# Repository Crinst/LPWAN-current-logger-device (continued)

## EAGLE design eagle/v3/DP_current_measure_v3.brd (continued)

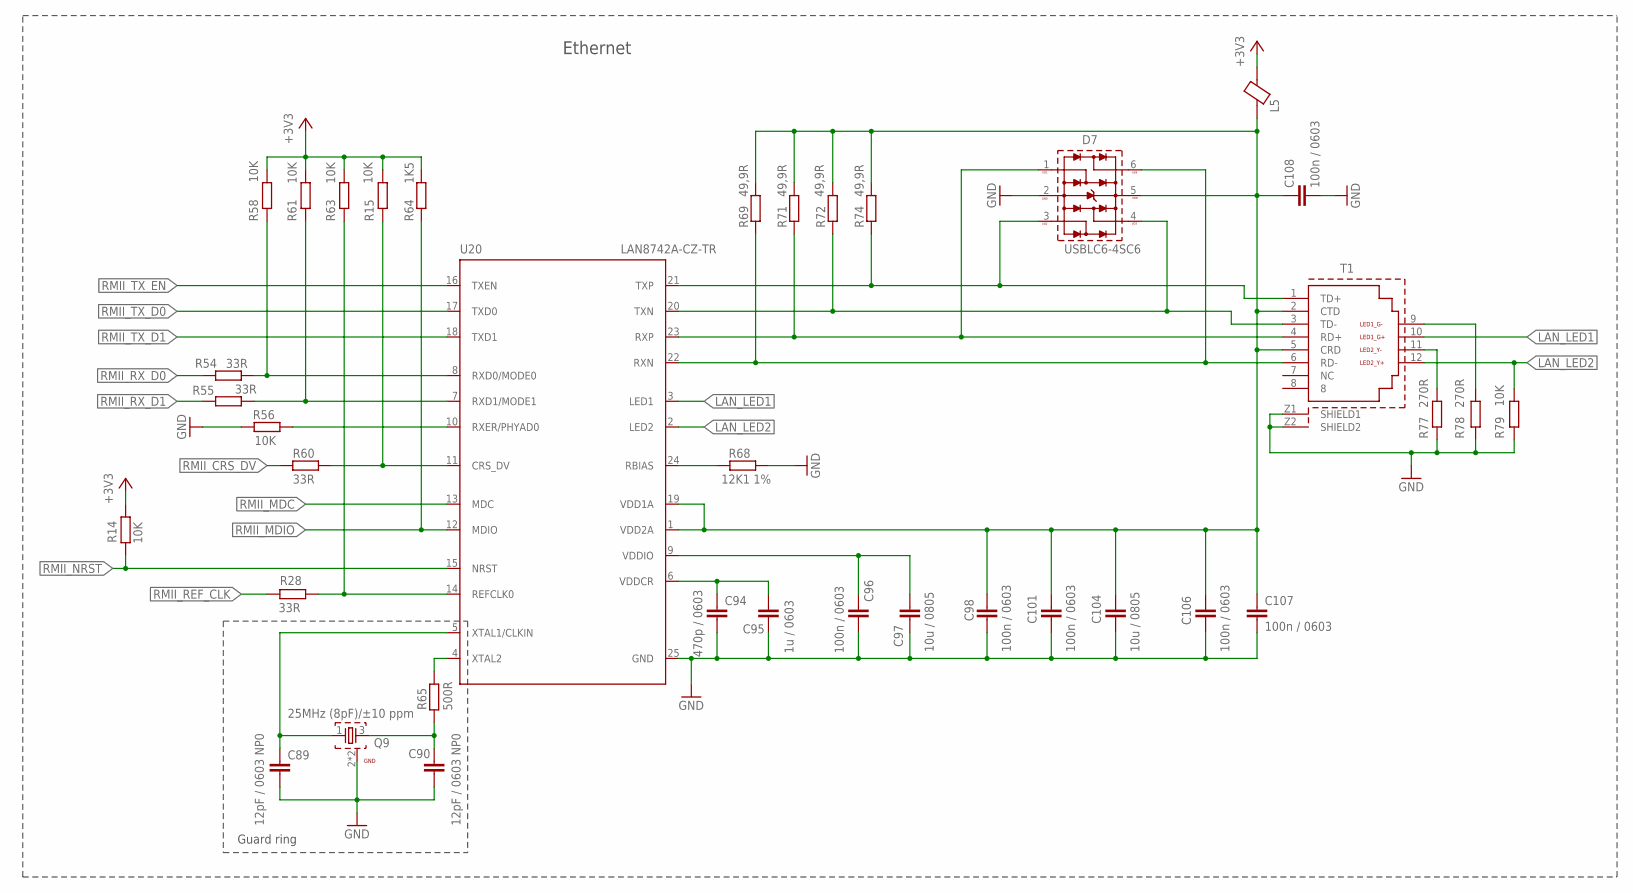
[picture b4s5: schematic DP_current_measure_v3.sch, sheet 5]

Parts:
C89, C90: 12pF / 0603 NP0; C0603
C94: 470p / 0603; C0603
C95: 1u / 0603; C0603
C96, C98, C101, C106, C107, C108: 100n / 0603; C0603
C97, C104: 10u / 0805; C0805
D7: USBLC6-4SC6; WE-TVS_SOT23-6L
L5: BLM21PG331SN1D
Q9: 25MHz (8pF)/±10 ppm; WE-XTAL_CFPX-218
R14, R15, R56, R58, R61, R63, R79: 10K; R0603
R28, R54, R55, R60: 33R; R0603
R64: 1K5; R0603
R65: 500R; R0603
R68: 12K1 1%; R0603
R69, R71, R72, R74: 49,9R; R0603
R77, R78: 270R; R0603
T1: WE-RJ45_7499010121A; 7499010121A
U20: LAN8742A-CZ-TR; 24-VFQFN

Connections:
+3V3: L5.1, R14.1, R15.1, R58.1, R61.1, R63.1, R64.1; also elsewhere on the board
GND: C89.2, C90.2, C94.2, C95.2, C96.2, C97.2, C98.2, C101.2, C104.2, C106.2, C107.2, C108.2, D7.2 (GND), Q9.2 (GND), Q9.4 (GND), R56.2, R68.1, R77.1, R78.1, R79.1, T1.Z1 (SHIELD1), T1.Z2 (SHIELD2), U20.25 (GND); also elsewhere on the board
LAN_LED1: T1.10 (LED1_G+), U20.3 (LED1)
LAN_LED2: R79.2, T1.12 (LED2_Y+), U20.2 (LED2)
unnamed: R78.2, T1.9 (LED1_G-)
unnamed: R65.1, U20.4 (XTAL2)
unnamed: R68.2, U20.24 (RBIAS)
unnamed: C98.1, C101.1, C104.1, C106.1, C107.1, C108.1, D7.5 (VDD), L5.2, R69.2, R71.2, R72.2, R74.2, T1.2 (CTD), T1.5 (CRD), U20.1 (VDD2A), U20.19 (VDD1A)
unnamed: C96.1, C97.1, U20.9 (VDDIO)
unnamed: C94.1, C95.1, U20.6 (VDDCR)
unnamed: C90.1, Q9.3 (2), R65.2
unnamed: C89.1, Q9.1, U20.5 (XTAL1/CLKIN)
unnamed: R77.2, T1.11 (LED2_Y-)
RMII_CRS_DV: R60.2; also elsewhere on the board
RMII_CRS_DV_: R15.2, R60.1, U20.11 (CRS_DV)
RMII_MDC: U20.13 (MDC); also elsewhere on the board
RMII_MDIO: R64.2, U20.12 (MDIO); also elsewhere on the board
RMII_NRST: R14.2, U20.15 (NRST)
RMII_REF_CLK: R28.2; also elsewhere on the board
RMII_REF_CLK_IC: R28.1, R63.2, U20.14 (REFCLK0)
RMII_RX_D0: R54.2; also elsewhere on the board
RMII_RX_D0_: R54.1, R58.2, U20.8 (RXD0/MODE0)
RMII_RX_D1: R55.2; also elsewhere on the board
RMII_RX_D1_: R55.1, R61.2, U20.7 (RXD1/MODE1)
RMII_RX_ER: R56.1, U20.10 (RXER/PHYAD0)
RMII_TX_D0: U20.17 (TXD0); also elsewhere on the board
RMII_TX_D1: U20.18 (TXD1); also elsewhere on the board
RMII_TX_EN: U20.16 (TXEN); also elsewhere on the board
RX_N: D7.6, R69.1, T1.6 (RD-), U20.22 (RXN)
RX_P: D7.1, R71.1, T1.4 (RD+), U20.23 (RXP)
TX_N: D7.4, R72.1, T1.3 (TD-), U20.20 (TXN)
TX_P: D7.3, R74.1, T1.1 (TD+), U20.21 (TXP)

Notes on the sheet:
Ethernet
Guard ring

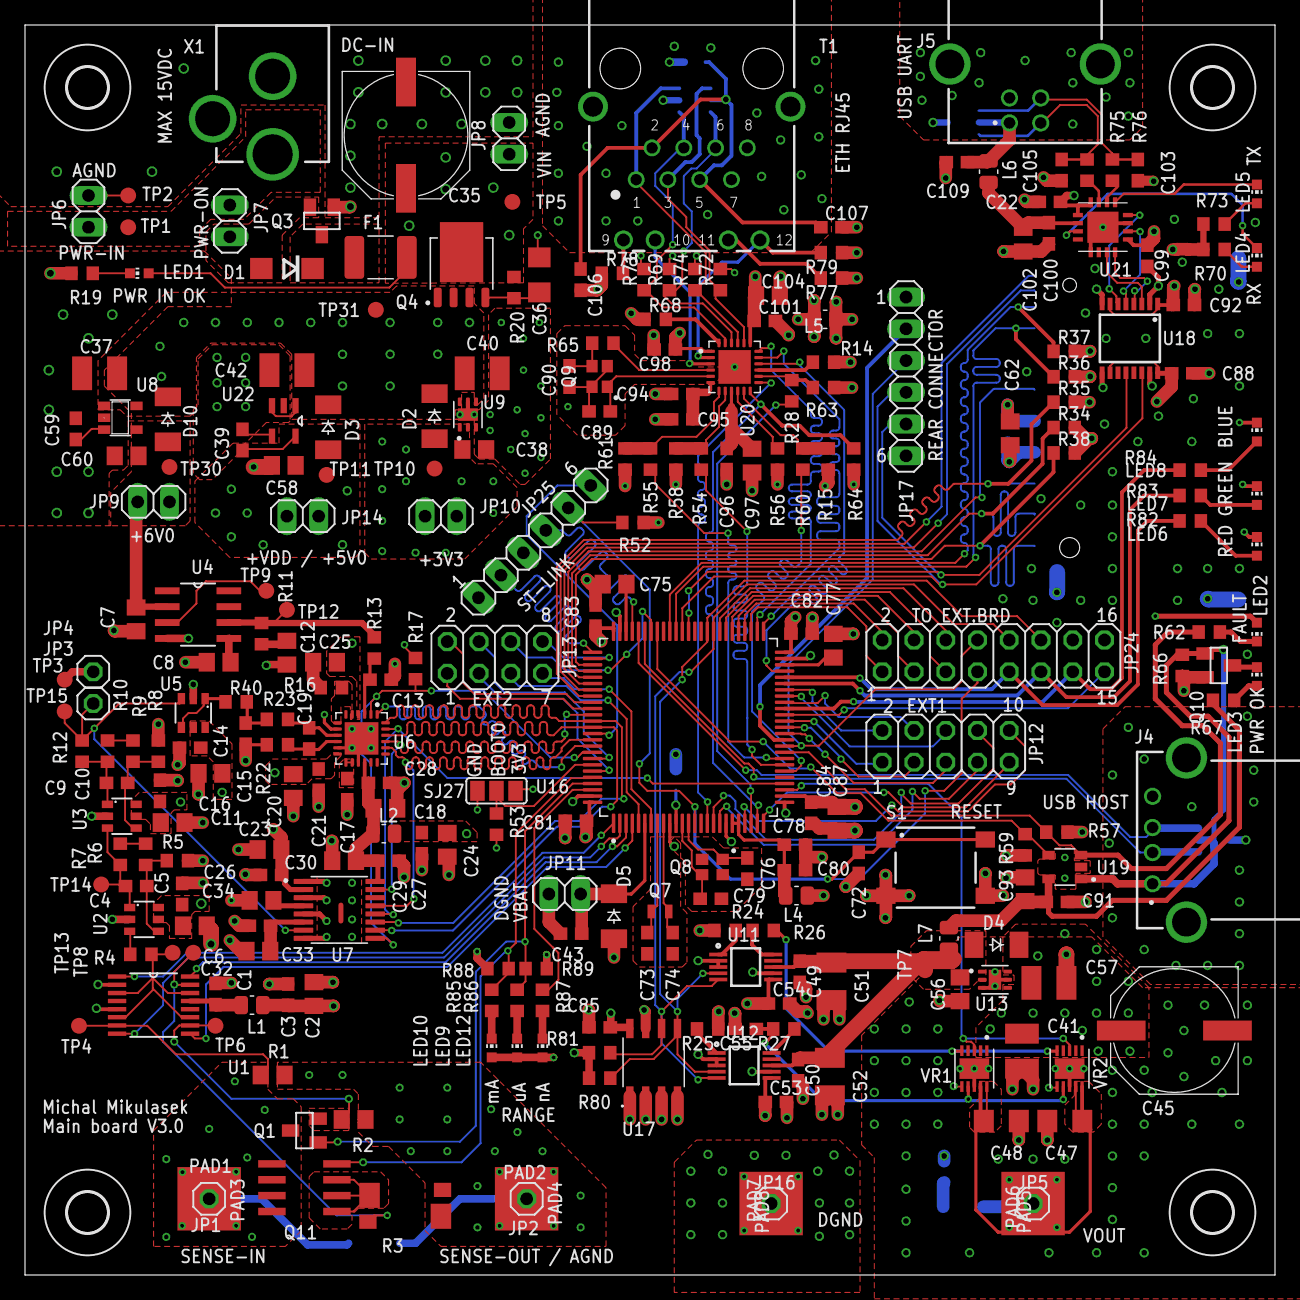
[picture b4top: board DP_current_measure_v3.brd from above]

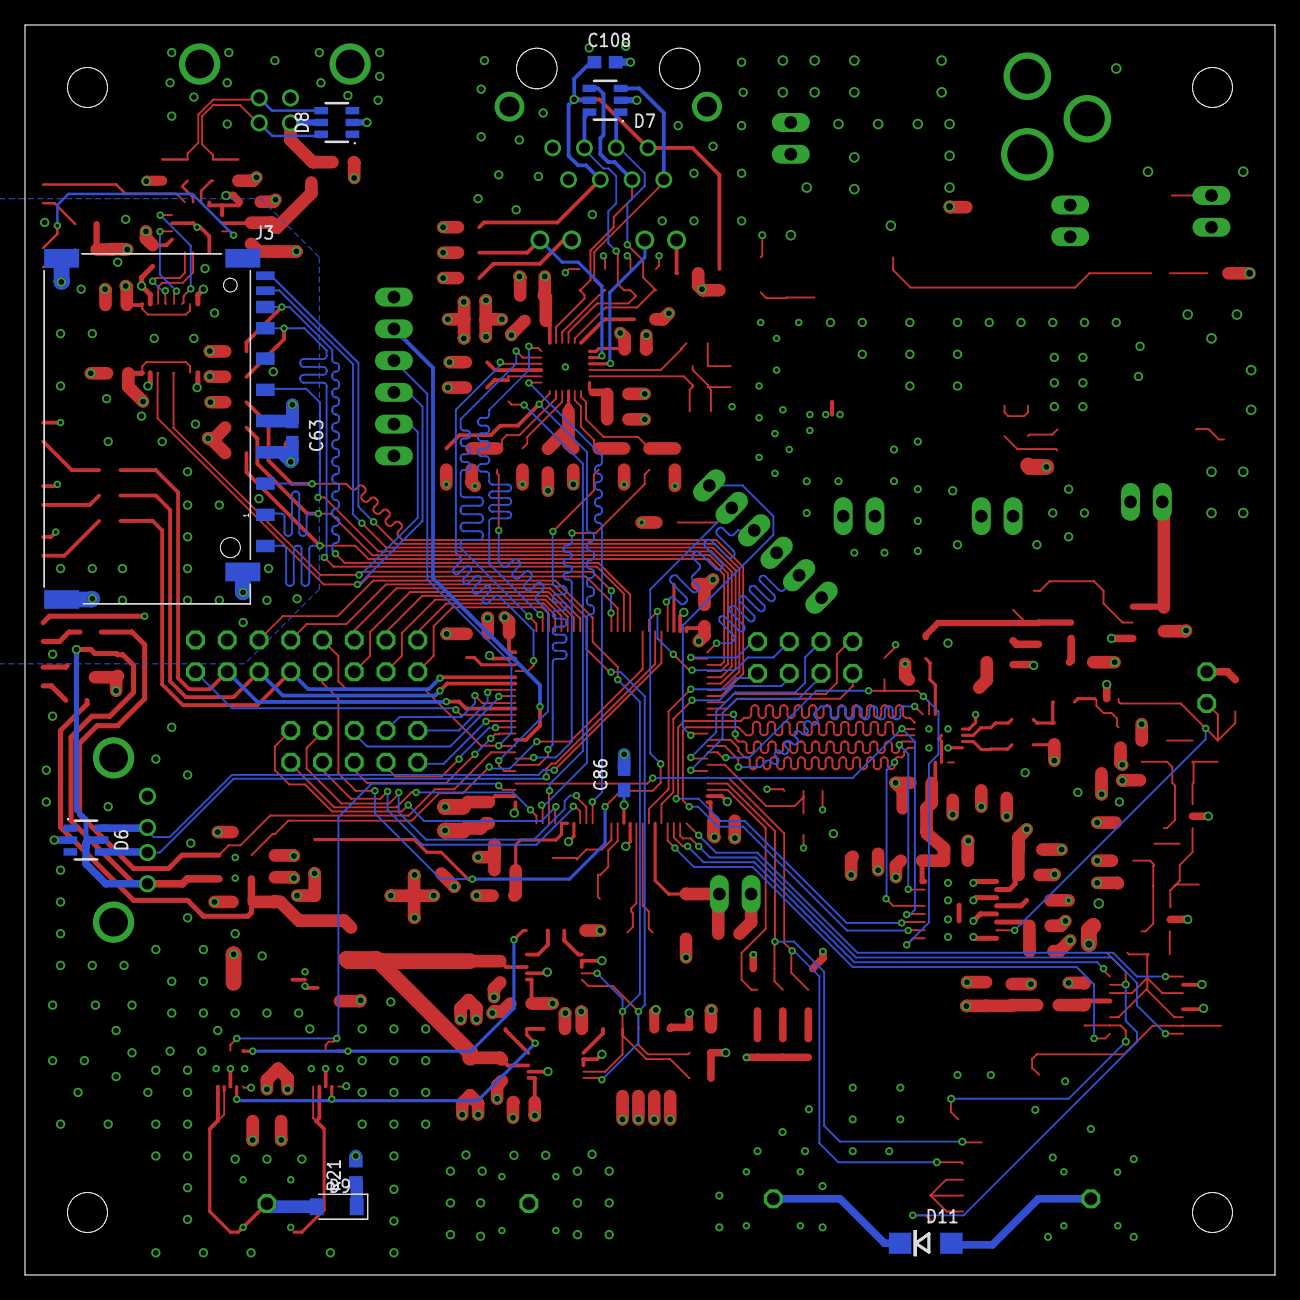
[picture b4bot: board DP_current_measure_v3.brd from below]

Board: 4 copper layers, 100.0 x 100.0 mm, 280 parts (10 on the bottom side), 183 nets.
